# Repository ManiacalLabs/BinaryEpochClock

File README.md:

BinaryEpochClock
================

**THIS MAY NOT BE THE FIRMWARE THAT CAME WITH YOUR CLOCK**

*We are constantly working on improving the firmware of our kits and the firmware contained in this repository may not be the same as that which came pre-programmed on your Binary Epoch Clock Kit.*

There are a few improvements over the original v1.0 Firmware

- Based on changes suggested by [kredal](https://github.com/kredal/) there is an alternte clock face to make the clock face a little more readable. Use the following key to make it a little easier to read: http://maniacallabs.com/misc/Binary_Clock_Key.png
- A 1D Pong face is now included - It is not playable, just sit back and enjoy the game.
- Short press A in order to switch between the three clock faces

The Binary Epoch Clock is a new twist on the old binary clock idea. Instead of just showing the individual digits as binary values, it show [Unix Epoch](http://en.wikipedia.org/wiki/Unix_Epoch) time as a full 32-bit binary value. This unique timepiece will make a great addition to the desk of any computer, electronics, time, or binary geek.

It runs off of an ATMega328P which makes is both fully compatible with the Arduino IDE and easily hackable. Also built in is a DS1307 Real Time Clock chip and battery backup allowing the clock to keep accurate time even in the event of a power loss. The board includes both FTDI and ICSP headers to allow easy upload of new or modified firmware. It can be powered from any USB port or USB power adapter using the included Mini-USB cable.

The clock can bet set manually or via any 5V FTDI cable (not included) and our handy 'sync_time' script which is included in the code repository. See the [assembly and usage guide](http://maniacallabs.com/guides/binary-epoch-clock/) for instructions and a handy video detailing the manual setting procedure for the clock.

To download the firmware source and PCB design files, just click the "Download Zip" button at the right of the GitHub page.

Buy online at the [Maniacal Labs Store](http://maniacallabs.com/product/becv1/)

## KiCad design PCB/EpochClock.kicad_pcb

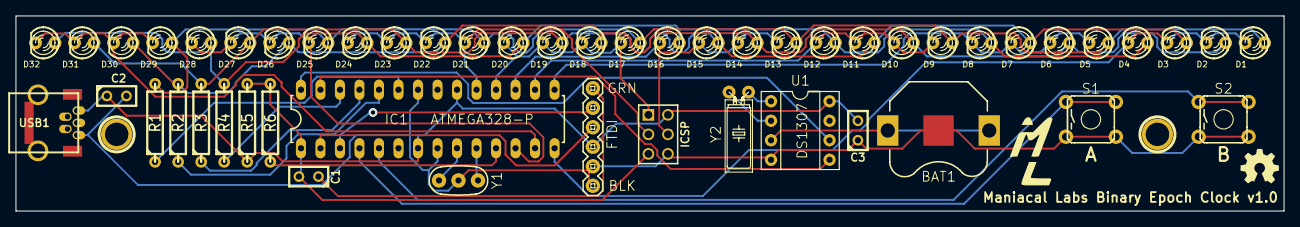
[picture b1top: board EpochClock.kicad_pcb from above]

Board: 2 copper layers, 165.1 x 25.4 mm, 53 parts (0 on the bottom side), 32 nets.

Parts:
1PIN, 2PIN: P***; 1pin
BAT1: BATTERY12PTH; fixed-SparkFun-BATTCON_12MM_PTH
C1, C2, C3: 0.1uF; C1
D1, D2, D3, D4, D5, D6, D7, D8, D9, D10, D11, D12, D13, D14, D15, D16, D17, D18, D19, D20, D21, D22, D23, D24, D25, D26, D27, D28, D29, D30, D31, D32: LED; LED-3MM
IC1: ATMEGA328-P; fixed_SparkFun-DIL28-3
JP1: FTDI; SparkFun-FTDI_BASIC_fixed
P1: ICSP; pin_array_3x2
R1, R2, R3, R4: 330; R4
R5: 10K; R4
R6: 110; R4
S1: A; SparkFun-TACTILE-PTH_fixed
S2: B; SparkFun-TACTILE-PTH_fixed
U1: DS1307; fixed_SparkFun-DIL08
USB1: USB-MINI-B; USB-MINI-B-CIRCULAR_PADS
Y1: RESONATOR-16MHZ; FIXED_SparkFun-RESONATOR-PTH
Y2: CRYSTALTC38H; fixed_SparkFun-TC38H

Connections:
5VCC: C2.1, C3.2, IC1.7, IC1.20, JP1.VCC, P1.2, R5.1, U1.8, USB1.1
GND: BAT1.GND, C2.2, C3.1, IC1.8, IC1.22, JP1.CTS, JP1.GND, P1.6, S1.3, S1.4, S2.3, S2.4, U1.4, USB1.5, Y1.2
MISO: D17.2, D18.2, D19.2, D20.2, IC1.18, P1.1
MOSI: D13.2, D14.2, D15.2, D16.2, IC1.17, P1.4
unnamed: BAT1.VCC@, U1.3
unnamed: U1.1, Y2.1
unnamed: U1.2, Y2.2
unnamed: C1.1, JP1.DTR
unnamed: IC1.11, R6.1
unnamed: D1.1, D5.1, D9.1, D13.1, D17.1, D21.1, D25.1, D29.1, R1.2
unnamed: D2.1, D6.1, D10.1, D14.1, D18.1, D22.1, D26.1, D30.1, R2.2
unnamed: D3.1, D7.1, D11.1, D15.1, D19.1, D23.1, D27.1, D31.1, R3.2
unnamed: D4.1, D8.1, D12.1, D16.1, D20.1, D24.1, D28.1, D32.1, R4.2
unnamed: D9.2, D10.2, D11.2, D12.2, IC1.16
unnamed: D29.2, D30.2, D31.2, D32.2, IC1.13
unnamed: D25.2, D26.2, D27.2, D28.2, IC1.12
unnamed: IC1.24, R2.1
unnamed: IC1.23, R1.1
unnamed: D5.2, D6.2, D7.2, D8.2, IC1.15
unnamed: D1.2, D2.2, D3.2, D4.2, IC1.14
unnamed: IC1.26, R4.1
unnamed: IC1.25, R3.1
PD2: IC1.4, S1.1, S1.2
PD3: IC1.5, S2.1, S2.2
RST: C1.2, IC1.1, P1.5, R5.2, R6.2
RXI: IC1.3, JP1.RXI
SCK: D21.2, D22.2, D23.2, D24.2, IC1.19, P1.3
SCL: IC1.28, U1.6
SDA: IC1.27, U1.5
TOSC1: IC1.9, Y1.3
TOSC2: IC1.10, Y1.1
TX0: IC1.2, JP1.TXO

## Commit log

2013-08-13 initial GitHub commit of firmware and pcb designs
2013-08-24 added .gitignore
2013-08-31 Update BinaryEpochClock.ino
    Replaced the very simple STATE_NONE with the Josh Rox mod, making a semi-readable clock.
2013-08-31 Update BinaryEpochClock.ino
    defined variables inline. This ain't perl.
2013-08-31 Update BinaryEpochClock.ino
    fixed time constructs.
2013-08-31 Few changes from Josh's code and adding short tap of A to change modes
2013-08-31 updated to denote this is an alternate firmware
2013-10-06 completed Sub Binary mode
2013-10-06 working 1D pong mode
2013-10-06 Updated README.md to mention new faces
2013-10-06 updated version
2013-10-06 fixed typo
